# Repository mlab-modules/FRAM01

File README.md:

# MLAB module with FRAM memory - CY15B108QN

The MLAB module with FRAM ([Ferroelectric Random Access Memory](https://en.wikipedia.org/wiki/Ferroelectric_RAM)) [CY15B108QN](https://www.infineon.com/dgdl/Infineon-CY15B108QN_CY15V108QN_Excelon(TM)_LP_8-Mbit_(1024K_X_8)_Serial_(SPI)_F-RAM-DataSheet-v11_00-EN.pdf?fileId=8ac78c8c7d0d8da4017d0ee7134b6ff4) provides a unique combination of features that outperform traditional forms of non-volatile memories such as Flash or EEPROM.

## Advantages of FRAM memory

FRAM, also known as Ferroelectric Random Access Memory, offers a range of key advantages that differentiate it and make it suitable for various applications:

1. **Fast data write**: FRAM allows fast data write with speeds comparable to the read speed. This property is much faster than writing data to Flash or EEPROM memories. 

2. **Low power consumption**: The process of writing to FRAM requires less energy than writing to Flash or EEPROM memories due to high speed. 

3. **Very high write/read cycles**: FRAM can undergo approximately 10¹⁵ write and read cycles, which is much more than other forms of non-volatile memories.

4. **High radiation resistance**: Due to its unique physical operation principle, FRAM is more resistant to radiation than other types of memories. The ferroelectric material used to store data can hold an electrical charge without the need for power. This means that once a bit is written to a memory cell, it stays there until something physically changes it. This property, known as polarization, allows FRAM to resist ionizing radiation that can cause random changes in the value of the charge in other types of memories.

For a more comprehensive understanding of FRAM, you can refer to the [FRAM Wikipedia page](https://en.wikipedia.org/wiki/Ferroelectric_RAM).

## Suitable use cases for FRAM memory

Thanks to these unique properties, FRAM is suitable for a range of applications, including:

1. **Industrial automation**: For quick data logging and applications that require a large number of writes.

2. **Energy measurement**: Where there is a need to write data quickly and frequently with low energy consumption.

3. **Automotive applications**: FRAM is resistant to radiation and temperature fluctuations, making it ideal for use in the automotive industry.

4. **Aerospace and defense applications**: Thanks to its resistance to ionizing radiation, FRAM is an ideal choice for applications that are exposed to high levels of radiation.

## Parameters of CY15B108QN FRAM memory

- Capacity: 8 Mbit (1024K x 8)
- Power supply: 1.8V to 3.6V
- Interface: SPI, up to 40 MHz
- Write speed: 14 ns
- Endurance: 10^15 write and read cycles
- Data retention: 151 years at 85°C

For detailed information on CY15B108QN FRAM memory, please refer to the [datasheet](https://www.infineon.com/dgdl/Infineon-CY15B108QN_CY15V108QN_Excelon(TM)_LP_8-Mbit_(1024K_X_8)_Serial_(SPI)_F-RAM-DataSheet-v11_00-EN.pdf?fileId=8ac78c8c7d0d8da4017d0ee7134b6ff4).

This module is perfectly tailored for demanding applications that require high write speed, high reliability and durability, and low power consumption. Take advantage of the benefits of FRAM memory in the MLAB module with CY15B108QN.

## Module schematics

## Overview of the MLAB module form factor

The [MLAB](https://mlab.cz/) modules provide a standard for developing modular solutions. They offer versatile usage as they can be either standalone modules for specific tasks or used as building blocks for more complex systems. The compact form factor along with the robust design of the MLAB modules ensures their effectiveness in a variety of applications. The MLAB system contains a wide range of electronic modules, each serving a specific function, which allows for great flexibility in designing electronic systems.

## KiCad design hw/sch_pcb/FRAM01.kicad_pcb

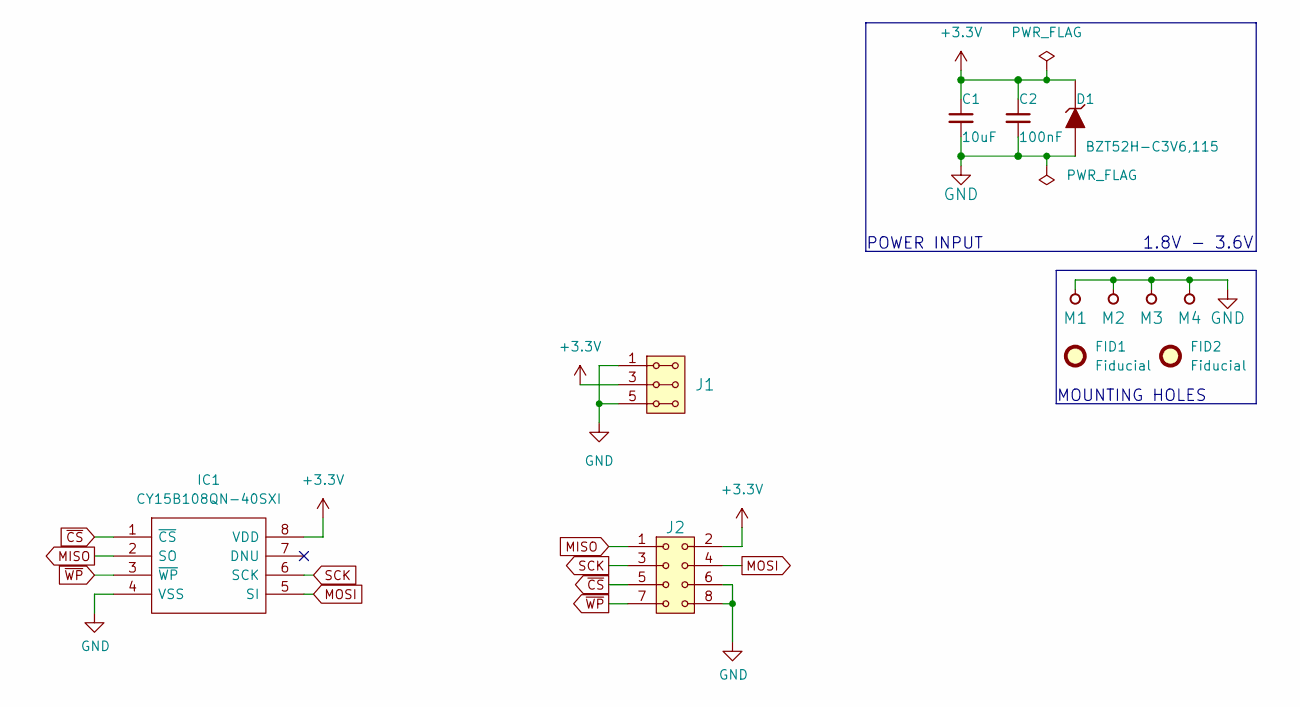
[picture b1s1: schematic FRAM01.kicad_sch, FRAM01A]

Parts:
C1: 10uF; C_0805_2012Metric
C2: 100nF; C_0805_2012Metric
D1: BZT52H-C3V6,115; D_SOD-123F
FID1, FID2: Fiducial; Fiducial_1mm_Mask2mm
IC1: CY15B108QN-40SXI; SOIC127P800X203-8N; Mouser Part Number 727-CY15B108QN-40SXI
J1: HEADER_2x03_PARALLEL; PinHeader_2x03_P2.54mm_Vertical
J2: HEADER_2x04; PinHeader_2x04_P2.54mm_Vertical
M1, M2: HOLE M3; MountingHole_3mm
M3, M4: HOLE; MountingHole_3mm

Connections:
+3.3V: C1.1, C2.1, D1.1 (K), IC1.8 (VDD), J1.3, J1.4, J2.2
GND: C1.2, C2.2, D1.2 (A), IC1.4 (VSS), J1.1, J1.2, J1.5, J1.6, J2.6, J2.8, M1.1, M2.1, M3.1, M4.1
MISO: IC1.2 (SO), J2.1
MOSI: IC1.5 (SI), J2.4
SCK: IC1.6 (SCK), J2.3
~CS: IC1.1 (~CS), J2.5
~WP: IC1.3 (~WP), J2.7

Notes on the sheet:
1.8V - 3.6V
POWER INPUT
MOUNTING HOLES

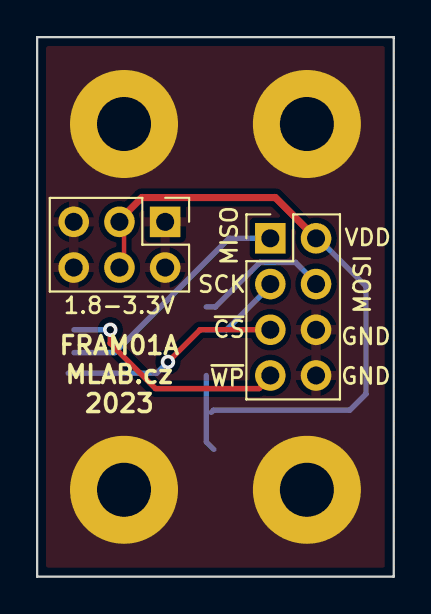
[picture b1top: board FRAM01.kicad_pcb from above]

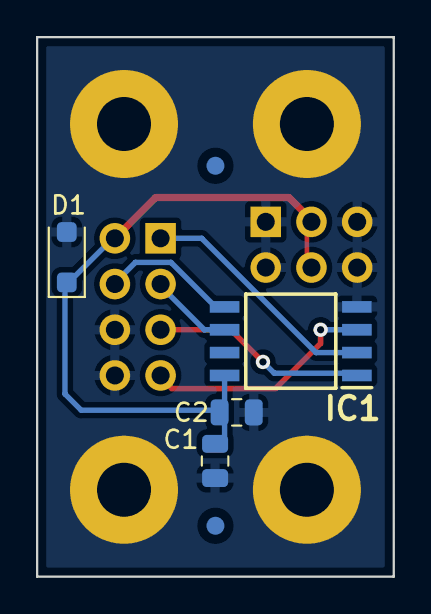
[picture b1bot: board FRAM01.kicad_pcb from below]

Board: 2 copper layers, 19.8 x 30.0 mm, 12 parts (6 on the bottom side), 7 nets.

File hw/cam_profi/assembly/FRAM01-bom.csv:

Component,Description,Part,References,Value,Footprint,Quantity Per PCB,Datasheet,ust_id,height,manufacturer_name,manufacturer_part_number,mouser part number,mouser price/stock
1,,C_Small-Device-ISM02A-rescue,C2,100nF,C_0805_2012Metric,1,,5c70984712875079b91f8b4c,,,,,
2,,C_Small-Device-ISM02A-rescue,C1,10uF,C_0805_2012Metric,1,,5c70984812875079b91f8bbe,,,,,
3,,D_ZENER-MLAB_D,D1,"BZT52H-C3V6,115",D_SOD-123F,1,"BZT52H-C3V6,115",650b35ab462c6d9e720543d0,,,,,
4,F-RAM Excelon LP 40 MHz 8-EIAJ,CY15B108QN-40SXI,IC1,CY15B108QN-40SXI,SOIC127P800X203-8N,1,https://www.mouser.in/datasheet/2/196/CYPR_S_A0011123055_1-3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,650b3dae462c6d9e72054477,2.03,Infineon / Cypress,CY15B108QN-40SXI,727-CY15B108QN-40SXI,https://www.mouser.co.uk/ProductDetail/Infineon-Cypress/CY15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
5,"2x03 2.54 mm pitch header, 2 pins next to each other are connected",HEADER_2x03_PARALLEL,J1,HEADER_2x03_PARALLEL,PinHeader_2x03_P2.54mm_Vertical,1,,,,,,,
6,2x04 2.54 mm pitch header,HEADER_2x04,J2,HEADER_2x04,PinHeader_2x04_P2.54mm_Vertical,1,,,,,,,

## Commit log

2023-01-12 Add files via upload
    KiCAD schematics
2023-01-16 pcb layout
2023-01-17 thicker traces
2023-01-19 Enable github actions. Change repository structure.
2023-01-19 Update actions products
2023-04-13 pcb layout update, ready for check
2023-04-13 smaller pcb layout 1x2
2023-05-25 automated commit; add github actions
2023-05-25 Update metadata files
2023-05-28 Update workflow files
2023-06-08 Fix DRC and ERC errors. Update title block.
2023-07-05 automated commit; rename source files to new naming convence
2023-09-06 power connection added, SPI connector changed
2023-09-06 change zener diode, minor improvements in silkscreen
2023-09-06 add fiducial
2023-09-07 Update README.md
    Improve headings
2023-09-07 Split silkscreen to avoid collision with vias. Update title-block
2023-09-07 power connection added, SPI connector changed, cherrypick, simple repairs
2023-09-16 Update image to image_title
2023-09-16 Update status
2023-09-20 add ustid
2023-09-20 fram layout
2023-09-22 Kontrola a upravy PCB pred vyrobou
2023-10-04 Edit B.Fab
